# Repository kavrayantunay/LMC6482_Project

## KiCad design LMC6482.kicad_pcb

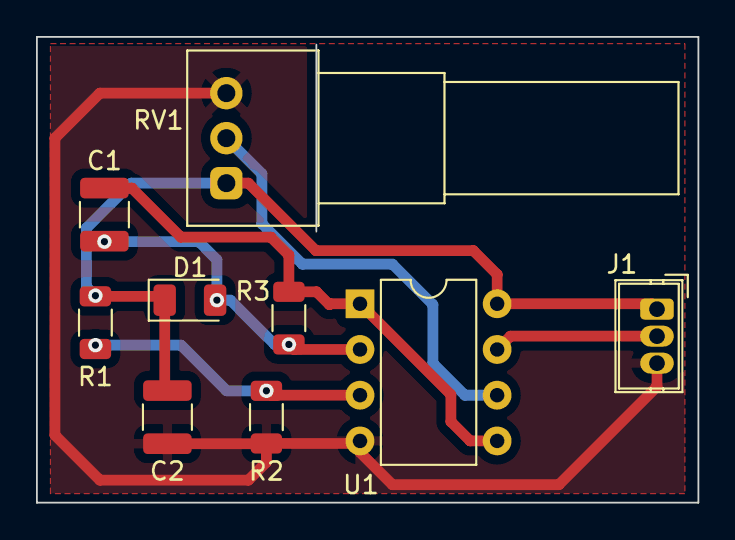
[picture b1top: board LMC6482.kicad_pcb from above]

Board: 2 copper layers, 36.8 x 25.9 mm, 9 parts (0 on the bottom side), 7 nets.

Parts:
C1: 100nF; C_1210_3225Metric
C2: 1uF; C_1210_3225Metric
D1: LED; LED_1206_3216Metric
J1: Conn_01x03; Wuerth_WR-WTB_64800311622_1x03_P1.50mm_Vertical
R1, R2: 10K; R_1206_3216Metric
R3: 5.1M; R_1206_3216Metric
RV1: R_Potentiometer; Potentiometer_Alps_RK097_Single_Horizontal
U1: LMC6482; DIP-8_W7.62mm

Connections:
+3.3V: C2.2, D1.1 (K), J1.1, R1.2, RV1.1, U1.8 (V+)
/Vout: J1.2, U1.7
GND: C2.1, J1.3, R2.1, RV1.3, U1.4 (V-)
unnamed: C1.1, D1.2 (A), R3.1, U1.2 (-)
unnamed: C1.2, R3.2, U1.1, U1.5 (+)
unnamed: R1.1, R2.2, U1.3 (+)
unnamed: RV1.2, U1.6 (-)
